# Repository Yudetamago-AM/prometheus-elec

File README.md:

# tanekonsat2022_runback

第19回（2023年度）種子島ロケットコンテストに出場予定の自動誘導ランバック機体の電装（回路・AW）ファイルを管理するレポジトリです。

構造のファイルは、<https://github.com/Yudetamago-AM/tanekonsat2022_runback>に、プログラムのファイルは色々のレポジトリに分散して管理してあります。

## KiCadで作業する時の注意

kicad2/lib/以下のtanekonsatというシンボルライブラリ・フットプリントライブラリを追加してあげる必要があります。

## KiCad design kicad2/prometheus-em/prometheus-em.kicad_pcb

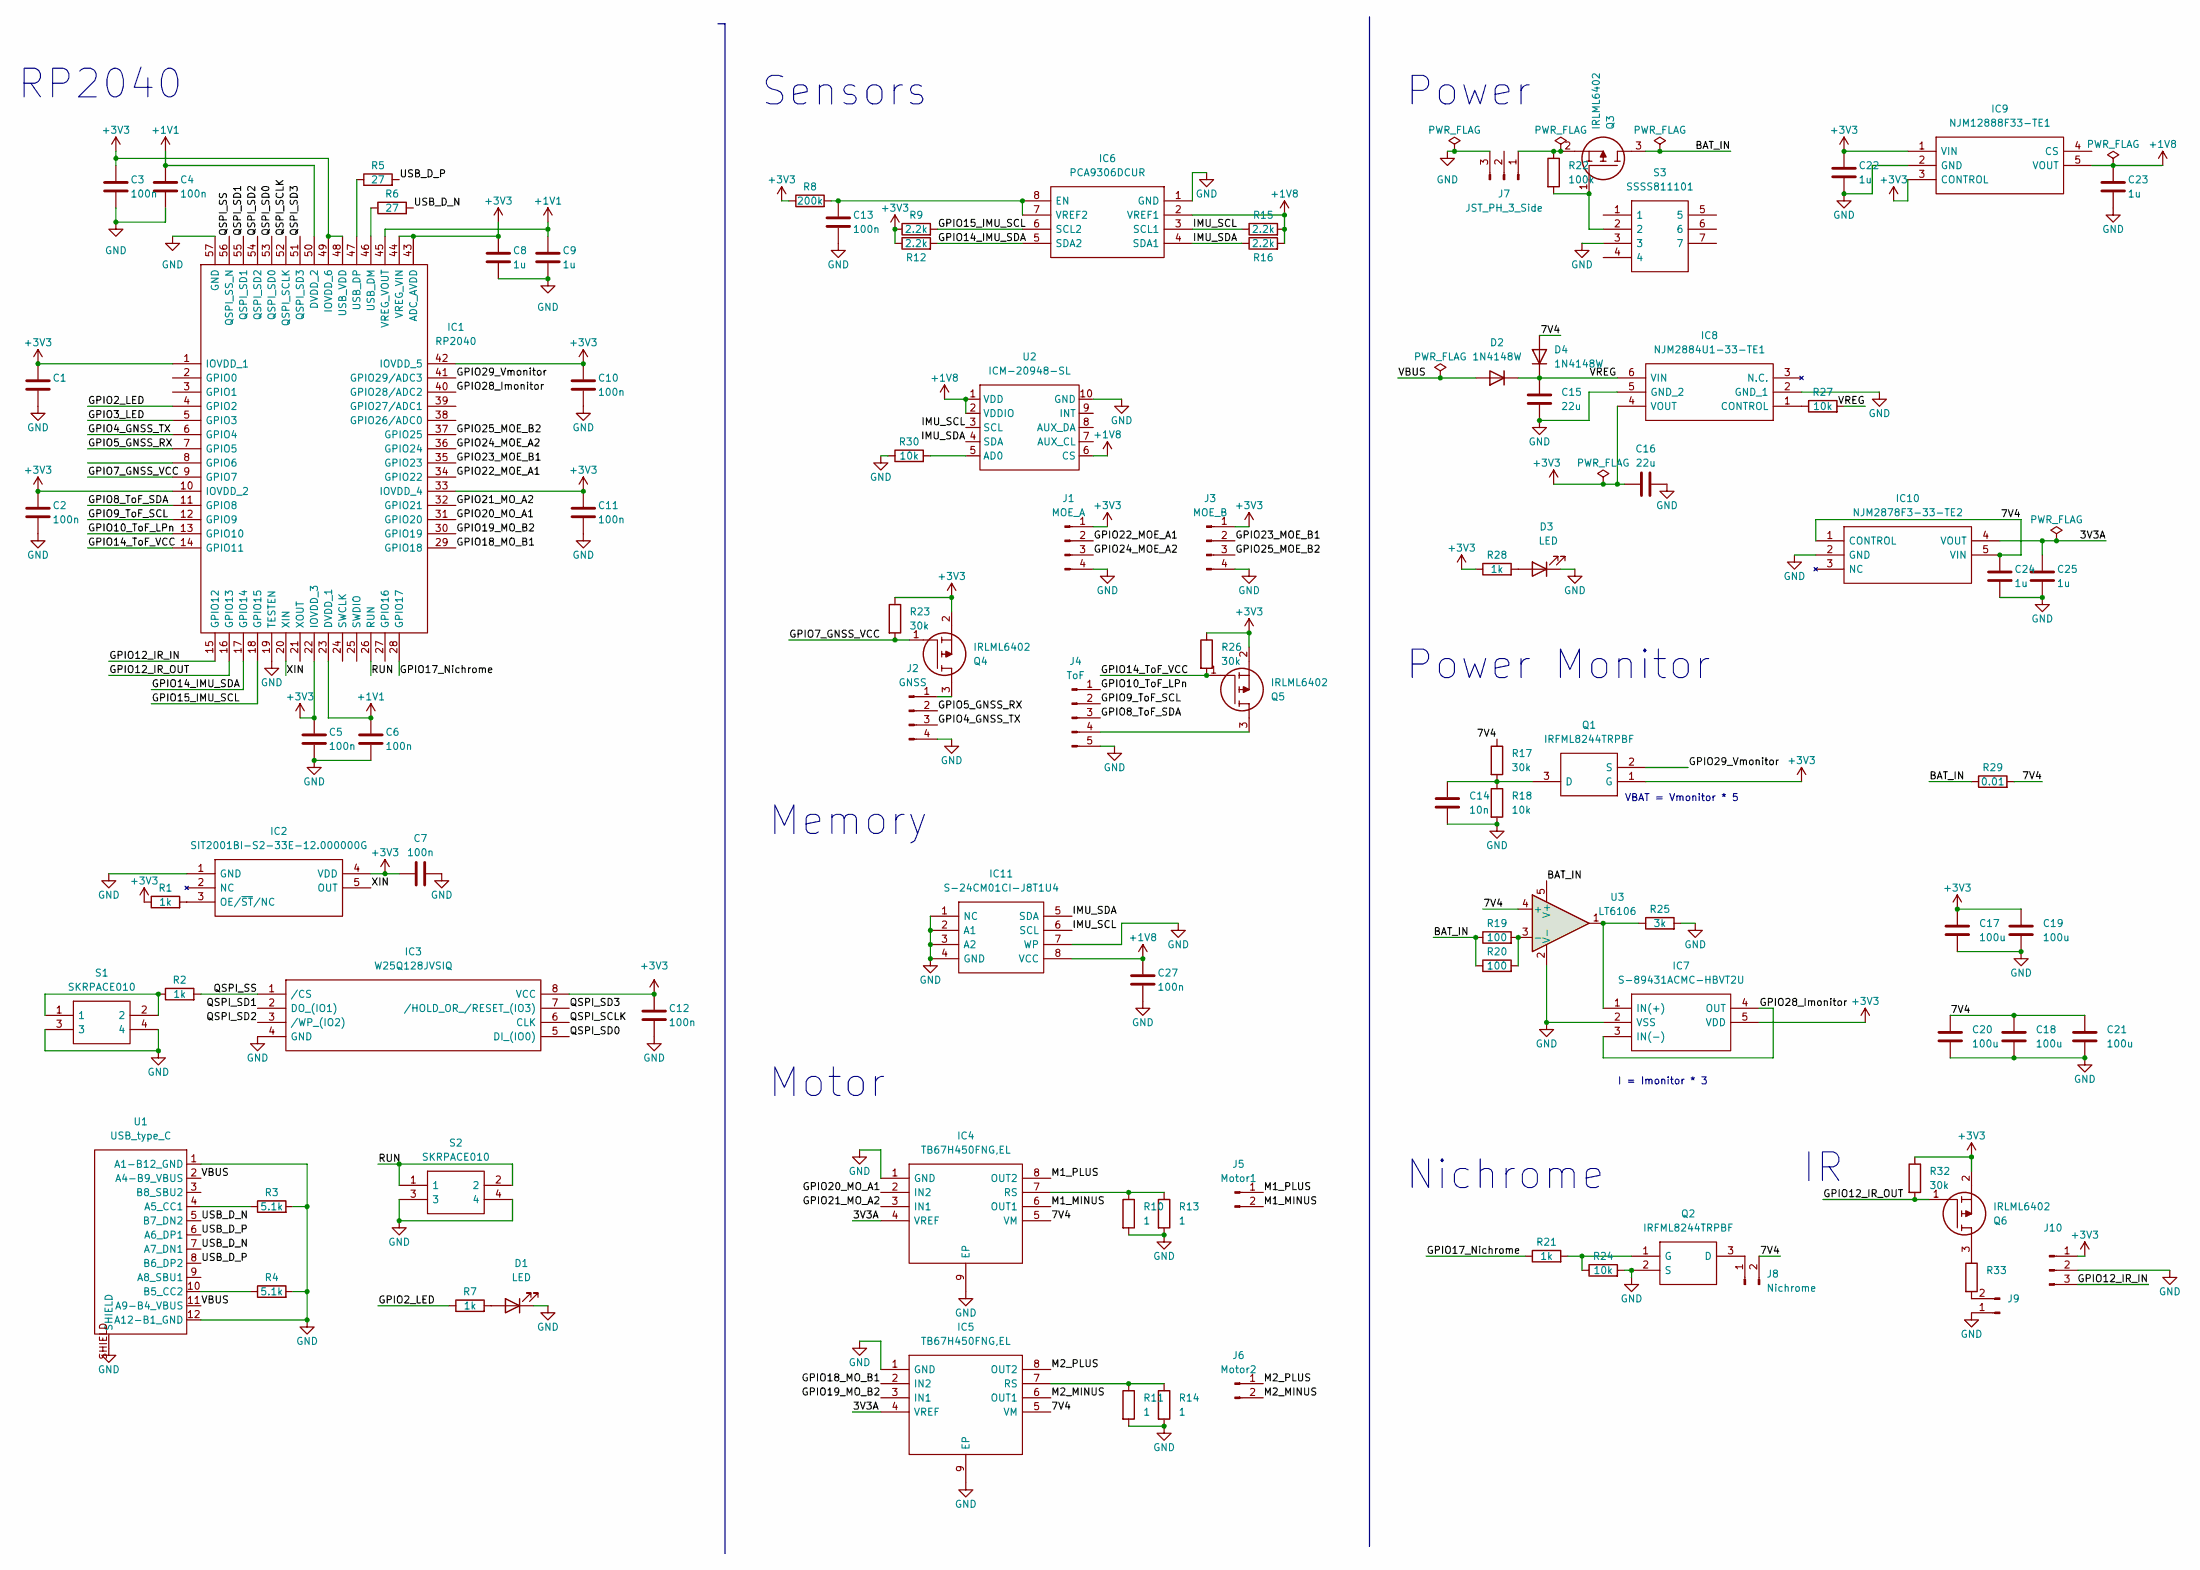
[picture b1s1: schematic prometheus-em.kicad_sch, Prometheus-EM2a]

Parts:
C1: LCSC C307331
C2, C3, C4, C7, C11, C12, C13: 100n; C_0402_1005Metric; LCSC C307331
C5, C6, C10, C27: 100n; C_0603_1608Metric
C8, C9, C22, C23, C24, C25: 1u; C_0402_1005Metric; LCSC C52923
C14: 10n; C_0402_1005Metric; LCSC C15195
C15, C16: 22u; C_0603_1608Metric; LCSC C59461
C17, C18, C19, C20, C21: 100u; C_1206_3216Metric
D1, D3: LED; LED_0603_1608Metric; LCSC C72041
D2, D4: 1N4148W; D_SOD-123
IC1: RP2040; QFN40P700X700X90-57N-D; Manufacturer_Part_Number RP2040; LCSC C2040
IC2: SIT2001BI-S2-33E-12.000000G; SOT95P280X130-5N; Manufacturer_Part_Number SIT2001BI-S2-33E-12.000000G; Mouser Part Number 788-2001BIS233E120G
IC3: W25Q128JVSIQ; SOIC127P790X216-8N; Manufacturer_Part_Number W25Q128JVSIQ; Mouser Part Number 454-W25Q128JVSIQ
IC4, IC5: TB67H450FNG,EL; SOIC127P600X175-9N; Manufacturer_Part_Number TB67H450FNG,EL
IC6: PCA9306DCUR; SOP50P310X90-8N; Manufacturer_Part_Number PCA9306DCUR; Mouser Part Number 595-PCA9306DCUR
IC7: S-89431ACMC-HBVT2U; SOT95P275X130-5N; Manufacturer_Part_Number S-89431ACMC-HBVT2U; Mouser Part Number 628-S89431ACMCHBVT2G
IC8: NJM2884U1-33-TE1; SOT-89-5-1; Manufacturer_Part_Number NJM2884U1-33-TE1; Mouser Part Number 513-NJM2884U1-33-TE1
IC9: NJM12888F33-TE1; SOT95P280X130-5N; Manufacturer_Part_Number NJM12888F33-TE1; Mouser Part Number 513-NJM12888F33-TE1
IC10: NJM2878F3-33-TE2; SOT65P210X100-5N; Manufacturer_Part_Number NJM2878F3-33-TE2; Mouser Part Number 513-NJM2878F3-33-TE2
IC11: S-24CM01CI-J8T1U4; SOT127P600X175-8N; Manufacturer_Part_Number S-24CM01CI-J8T1U4; Mouser Part Number 628-S-24CM01CIJ8T1U4
J1: MOE_A; PinHeader_1x04_P2.00mm_Vertical
J2: GNSS; JST_ZH_B4B-ZR_1x04_P1.50mm_Vertical
J3: MOE_B; PinHeader_1x04_P2.00mm_Vertical
J4: ToF; JST_ZH_B5B-ZR_1x05_P1.50mm_Vertical
J5: Motor1; PinHeader_1x02_P2.00mm_Vertical
J6: Motor2; PinHeader_1x02_P2.00mm_Vertical
J7: JST_PH_3_Side; JST_PH_S3B-PH-K_03x2.00mm_Angled
J8: Nichrome; PinHeader_1x02_P2.00mm_Vertical
J9, J10: (no value)
Q1, Q2: IRFML8244TRPBF; SOT95P237X112-3N; Manufacturer_Part_Number IRFML8244TRPBF; Mouser Part Number 942-IRFML8244TRPBF
Q3, Q4, Q5, Q6: IRLML6402; SOT95P237X112-3N; Manufacturer_Part_Number IRLML6402; Mouser Part Number N/A
R1, R2, R7, R21, R28: 1k; R_0402_1005Metric; LCSC C11702
R3, R4: 5.1k; R_0402_1005Metric; LCSC C25905
R5, R6: 27; R_0402_1005Metric; LCSC C174257
R8: 200k; R_0402_1005Metric; LCSC C25764
R9, R12, R15, R16: 2.2k; R_0402_1005Metric
R10, R11, R13, R14: 1; R_0603_1608Metric; LCSC C22936
R17, R23, R26, R32: 30k; R_0603_1608Metric; LCSC C22984
R18, R24, R27, R30: 10k; R_0402_1005Metric; LCSC C25744
R19, R20: 100; R_0402_1005Metric; LCSC C25076
R22: 100k; R_0402_1005Metric
R25: 3k; R_0603_1608Metric
R29: 0.01; R_1206_3216Metric
R33: (no value)
S1, S2: SKRPACE010; SMT_4.2X3.2_; Manufacturer_Part_Number SKRPACE010; Mouser Part Number 688-SKRPACE010
S3: SSSS811101; Manufacturer_Part_Number SSSS811101; Mouser Part Number 688-SSSS811101
U1: USB_type_C; USB_typeC_t
U2: ICM-20948-SL; ICM-20948_SL
U3: LT6106; SOT-23-5

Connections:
+1V1: C4.1, C6.1, C9.1, IC1.23 (DVDD_1), IC1.45 (VREG_VOUT), IC1.50 (DVDD_2)
+1V8: C23.1, C27.1, IC6.2 (VREF1), IC9.5 (VOUT), IC11.8 (VCC), R15.2, R16.2, U2.1 (VDD), U2.2 (VDDIO), U2.6 (CS)
+3V3: C1.1, C2.1, C3.1, C5.1, C7.1, C8.1, C10.1, C11.1, C12.1, C16.2, C17.1, C19.1, C22.1, IC1.1 (IOVDD_1), IC1.10 (IOVDD_2), IC1.22 (IOVDD_3), IC1.33 (IOVDD_4), IC1.42 (IOVDD_5), IC1.43 (ADC_AVDD), IC1.44 (VREG_VIN), IC1.48 (USB_VDD), IC1.49 (IOVDD_6), IC2.4 (VDD), IC3.8 (VCC), IC7.5 (VDD), IC8.4 (VOUT), IC9.1 (VIN), IC9.3 (CONTROL), J1.1, J3.1, J10.1, Q1.1 (G), Q4.2, Q5.2, Q6.2, R1.1, R8.1, R9.1, R12.1, R23.1, R26.1, R28.1, R32.1
/3V3A: C25.1, IC4.4 (VREF), IC5.4 (VREF), IC10.4 (VOUT)
/7V4: C18.1, C20.1, C21.1, C24.1, D4.2 (A), IC4.5 (VM), IC5.5 (VM), IC10.1 (CONTROL), IC10.5 (VIN), J8.2, R17.1, R29.2, U3.4 (+)
/BAT_IN: Q3.3, R19.1, R20.1, R29.1, U3.5 (V+)
/GPIO2_LED: IC1.4 (GPIO2), R7.1
/GPIO3_LED: IC1.5 (GPIO3)
/GPIO4_GNSS_TX: IC1.6 (GPIO4), J2.3
/GPIO5_GNSS_RX: IC1.7 (GPIO5), J2.2
/GPIO7_GNSS_VCC: IC1.9 (GPIO7), Q4.1, R23.2
/GPIO8_ToF_SDA: IC1.11 (GPIO8), J4.3
/GPIO9_ToF_SCL: IC1.12 (GPIO9), J4.2
/GPIO10_ToF_LPn: IC1.13 (GPIO10), J4.1
/GPIO12_IR_IN: IC1.15 (GPIO12), J10.3
/GPIO12_IR_OUT: IC1.16 (GPIO13), Q6.1, R32.2
/GPIO14_IMU_SDA: IC1.17 (GPIO14), IC6.5 (SDA2), R12.2
/GPIO14_ToF_VCC: IC1.14 (GPIO11), Q5.1, R26.2
/GPIO15_IMU_SCL: IC1.18 (GPIO15), IC6.6 (SCL2), R9.2
/GPIO17_Nichrome: IC1.28 (GPIO17), R21.1
/GPIO18_MO_B1: IC1.29 (GPIO18), IC5.2 (IN2)
/GPIO19_MO_B2: IC1.30 (GPIO19), IC5.3 (IN1)
/GPIO20_MO_A1: IC1.31 (GPIO20), IC4.2 (IN2)
/GPIO21_MO_A2: IC1.32 (GPIO21), IC4.3 (IN1)
/GPIO22_MOE_A1: IC1.34 (GPIO22), J1.2
/GPIO23_MOE_B1: IC1.35 (GPIO23), J3.2
/GPIO24_MOE_A2: IC1.36 (GPIO24), J1.3
/GPIO25_MOE_B2: IC1.37 (GPIO25), J3.3
/GPIO28_Imonitor: IC1.40 (GPIO28/ADC2), IC7.3 (IN(-)), IC7.4 (OUT)
/GPIO29_Vmonitor: IC1.41 (GPIO29/ADC3), Q1.2 (S)
/IMU_SCL: IC6.3 (SCL1), IC11.6 (SCL), R15.1, U2.3 (SCL)
/IMU_SDA: IC6.4 (SDA1), IC11.5 (SDA), R16.1, U2.4 (SDA)
/M1_MINUS: IC4.6 (OUT1), J5.2
/M1_PLUS: IC4.8 (OUT2), J5.1
/M2_MINUS: IC5.6 (OUT1), J6.2
/M2_PLUS: IC5.8 (OUT2), J6.1
/QSPI_SCLK: IC1.52 (QSPI_SCLK), IC3.6 (CLK)
/QSPI_SD0: IC1.53 (QSPI_SD0), IC3.5 (DI_(IO0))
/QSPI_SD1: IC1.55 (QSPI_SD1), IC3.2 (DO_(IO1))
/QSPI_SD2: IC1.54 (QSPI_SD2), IC3.3 (/WP_(IO2))
/QSPI_SD3: IC1.51 (QSPI_SD3), IC3.7 (/HOLD_OR_/RESET_(IO3))
/QSPI_SS: IC1.56 (QSPI_SS_N), IC3.1 (/CS), R2.2
/RUN: IC1.26 (RUN), S2.1, S2.2
/USB_D_N: R6.2, U1.5 (B7_DN2), U1.7 (A7_DN1)
/USB_D_P: R5.2, U1.6 (A6_DP1), U1.8 (B6_DP2)
/VBUS: D2.2 (A), U1.2 (A4-B9_VBUS), U1.11 (A9-B4_VBUS)
/VREG: C15.1, D2.1 (K), D4.1 (K), IC8.6 (VIN), R27.2
/XIN: IC1.20 (XIN), IC2.5 (OUT)
GND: C1.2, C2.2, C3.2, C4.2, C5.2, C6.2, C7.2, C8.2, C9.2, C10.2, C11.2, C12.2, C13.2, C14.2, C15.2, C16.1, C17.2, C18.2, C19.2, C20.2, C21.2, C22.2, C23.2, C24.2, C25.2, C27.2, D1.1 (K), D3.1 (K), IC1.19 (TESTEN), IC1.57 (GND), IC2.1 (GND), IC3.4 (GND), IC4.1 (GND), IC4.9 (EP), IC5.1 (GND), IC5.9 (EP), IC6.1 (GND), IC7.2 (VSS), IC8.2 (GND_1), IC8.5 (GND_2), IC9.2 (GND), IC10.2 (GND), IC11.1 (NC), IC11.2 (A1), IC11.3 (A2), IC11.4 (GND), IC11.7 (WP), J1.4, J2.4, J3.4, J4.5, J7.3, J9.1, J10.2, Q2.2 (S), R3.2, R4.2, R10.2, R11.2, R13.2, R14.2, R18.2, R24.2, R25.2, R30.1, S1.3, S1.4, S2.3, S2.4, S3.3, U1.1 (A1-B12_GND), U1.12 (A12-B1_GND), U1.SHIELD, U2.10 (GND), U3.2 (V-)
unnamed: C13.1, IC6.7 (VREF2), IC6.8 (EN), R8.2
unnamed: C14.1, Q1.3 (D), R17.2, R18.1
unnamed: D1.2 (A), R7.2
unnamed: D3.2 (A), R28.2
unnamed: IC1.46 (USB_DM), R6.1
unnamed: IC1.47 (USB_DP), R5.1
unnamed: IC2.3 (OE/~ST/NC), R1.2
unnamed: IC4.7 (RS), R10.1, R13.1
unnamed: IC5.7 (RS), R11.1, R14.1
unnamed: IC7.1 (IN(+)), R25.1, U3.1
unnamed: IC8.1 (CONTROL), R27.1
unnamed: J2.1, Q4.3
unnamed: J4.4, Q5.3
unnamed: J7.1, Q3.2, R22.1
unnamed: J8.1, Q2.3 (D)
unnamed: J9.2, R33.2
unnamed: Q2.1 (G), R21.2, R24.1
unnamed: Q3.1, R22.2, S3.2
unnamed: Q6.3, R33.1
unnamed: R2.1, S1.1, S1.2
unnamed: R3.1, U1.4 (A5_CC1)
unnamed: R4.1, U1.10 (B5_CC2)
unnamed: R19.2, R20.2, U3.3 (-)
unnamed: R30.2, U2.5 (AD0)

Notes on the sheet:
Power
RP2040
Nichrome
VBAT = Vmonitor * 5
Sensors
Motor
Memory
I = Imonitor * 3
Power Monitor

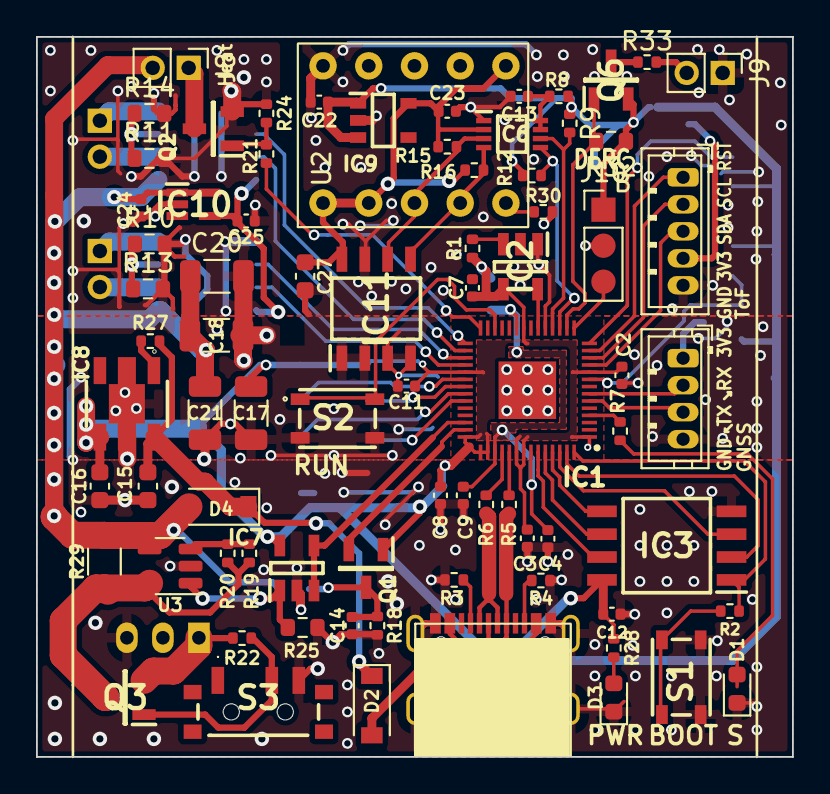
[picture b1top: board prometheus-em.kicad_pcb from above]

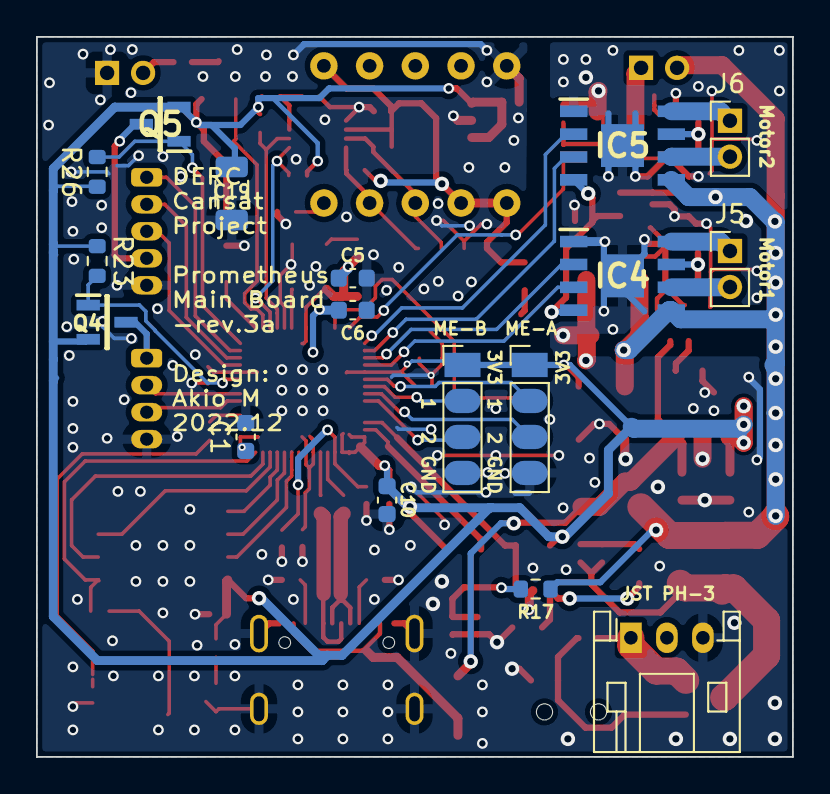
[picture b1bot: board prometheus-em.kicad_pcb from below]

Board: 2 copper layers, 42.0 x 40.0 mm, 95 parts (17 on the bottom side), 72 nets.

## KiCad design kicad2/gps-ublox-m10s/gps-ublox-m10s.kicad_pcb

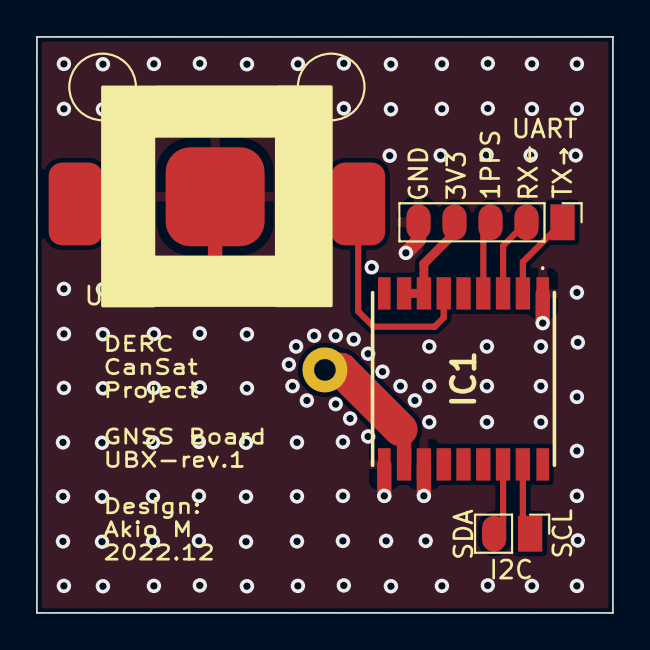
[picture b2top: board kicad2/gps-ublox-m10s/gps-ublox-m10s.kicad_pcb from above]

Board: 2 copper layers, 32.0 x 32.0 mm, 5 parts (1 on the bottom side), 9 nets.

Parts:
ANT1: CGGBP.25.4.A.02; CGGBP254A02
IC1: MAX-M10S-00B; MAXM10S00B
J1: Conn_01x05_Male; PinHeader_1x05_P2.00mm_Vertical
J2: I2C; PinHeader_1x02_P2.00mm_Vertical
U1: CR1025; CR1025_Holder

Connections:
+3V0: IC1.6 (V_BCKP), U1.2 (plus)
+3V3: IC1.7 (V_IO), IC1.8 (VCC), J1.4
/GNSS_1PPS: IC1.4 (TIMEPULSE), J1.3
/GNSS_RX: IC1.3 (RXD), J1.2
/GNSS_TX: IC1.2 (TXD), J1.1
/SCL: IC1.17 (SCL), J2.1
/SDA: IC1.16 (SDA), J2.2
GND: IC1.1 (GND_1), IC1.10 (GND_2), IC1.12 (GND_3), J1.5, U1.1 (minus)
unnamed: ANT1.1, IC1.11 (RF_IN)

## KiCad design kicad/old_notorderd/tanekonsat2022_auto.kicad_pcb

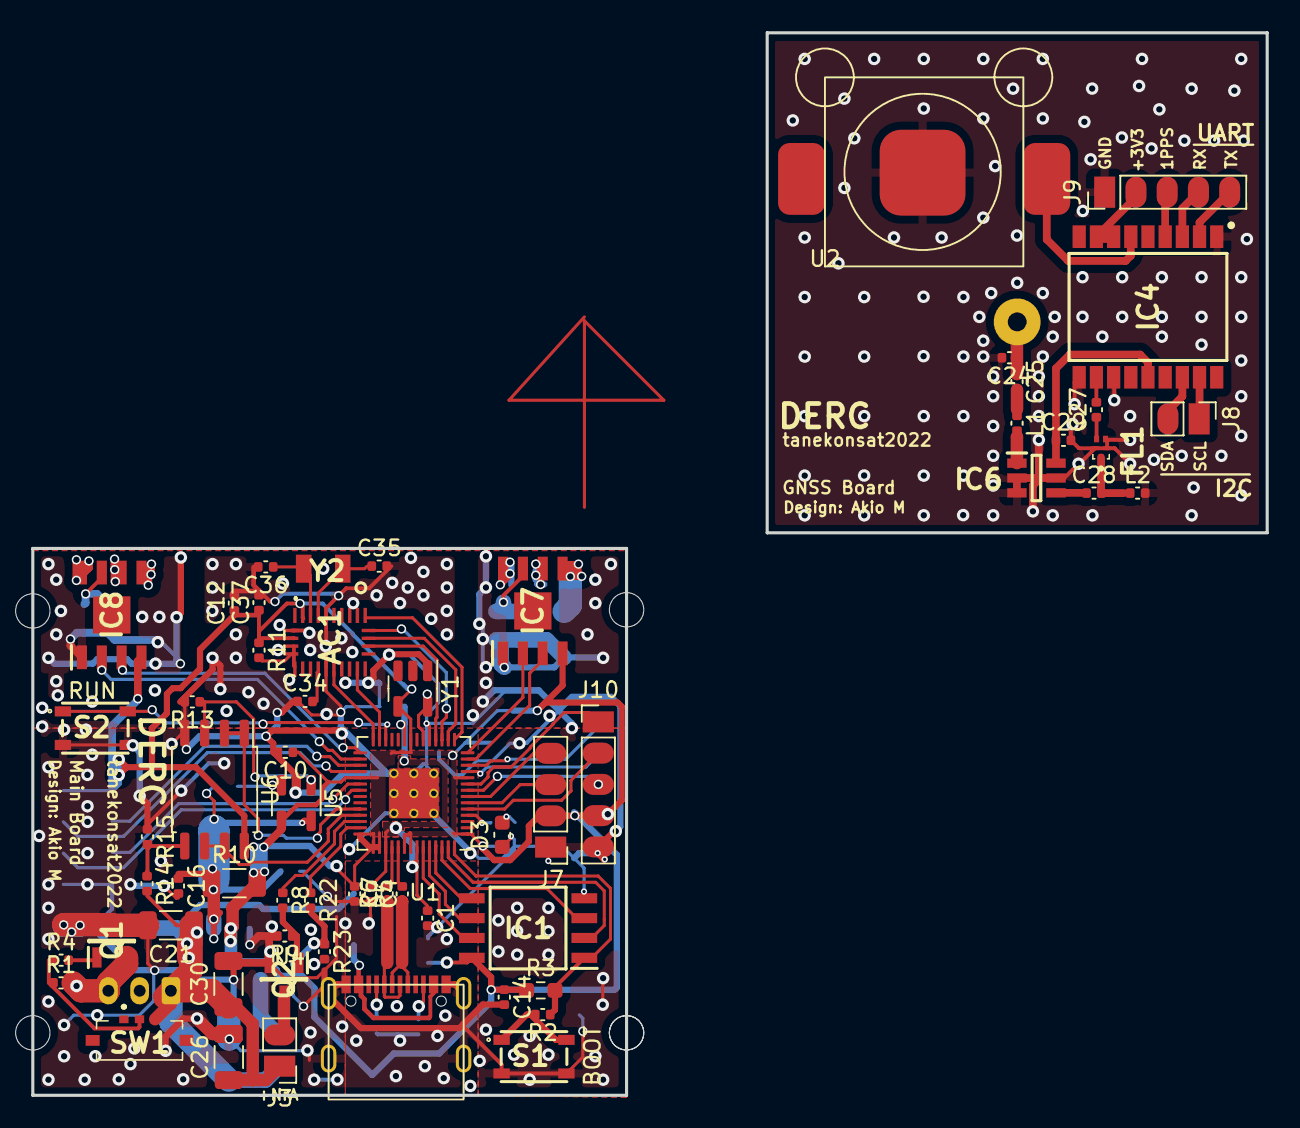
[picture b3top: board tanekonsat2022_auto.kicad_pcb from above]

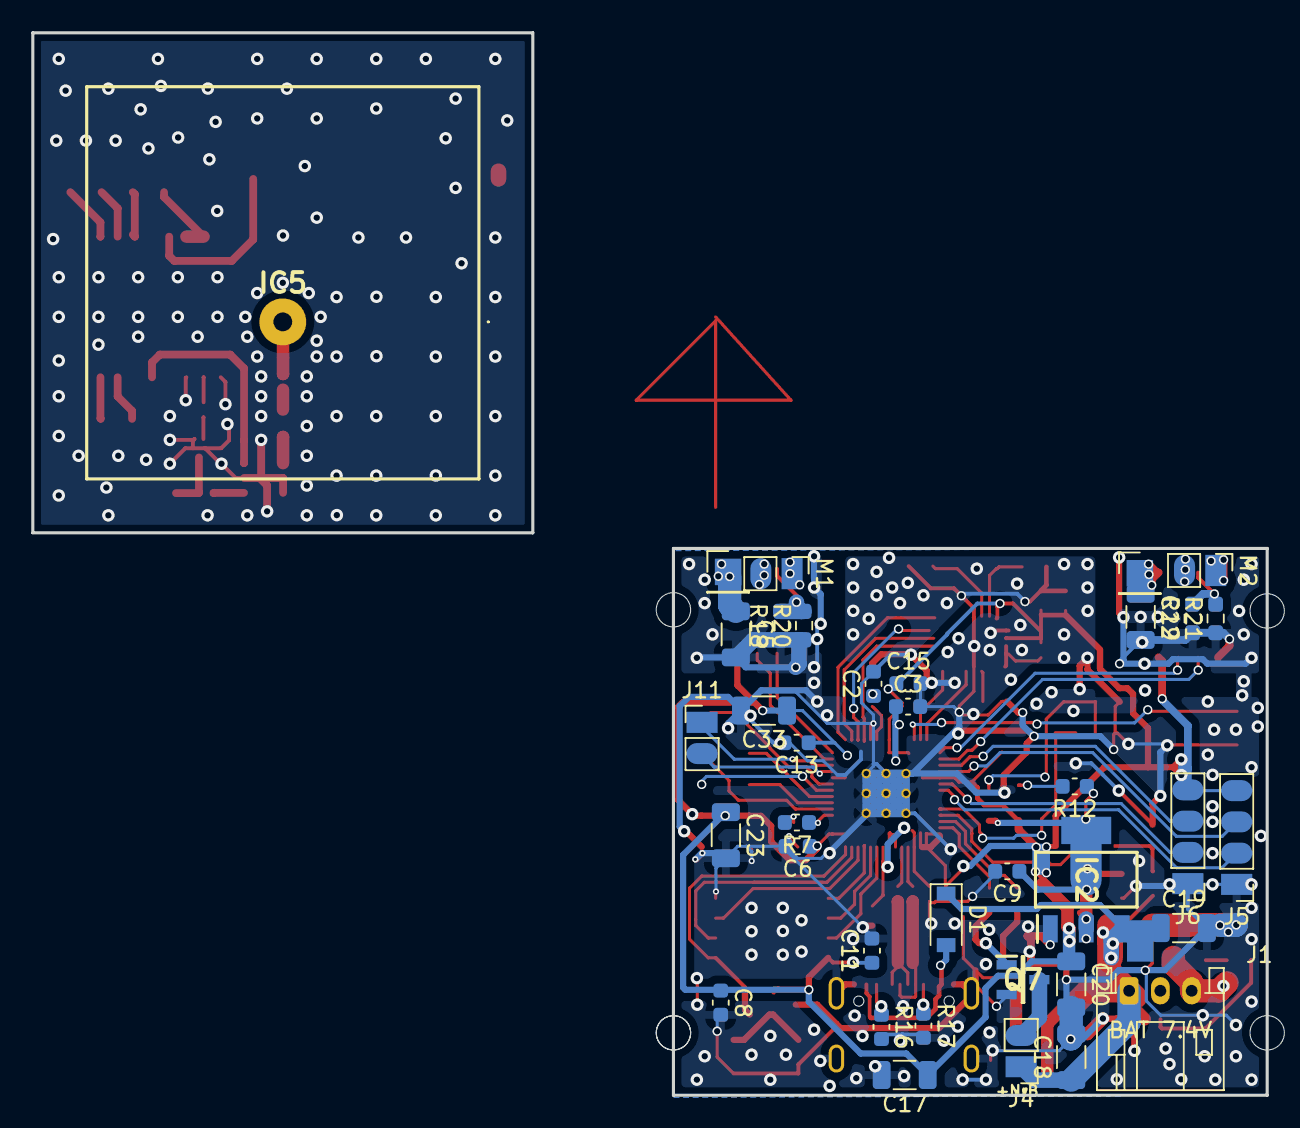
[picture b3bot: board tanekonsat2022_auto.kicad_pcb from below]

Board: 2 copper layers, 38.0 x 35.0 mm, 96 parts (35 on the bottom side), 80 nets.

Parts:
AC1: BNO085
C1, C10, C12, C14, C34, C37: 100n; C_0402_1005Metric
C2: 10p; C_0603_1608Metric
C3, C6, C8, C11, C13, C15: 100n; C_0603_1608Metric
C4, C7, C16: 1u; C_0402_1005Metric
C5, C17, C18, C19, C20, C21, C22, C23, C26, C30, C33: 100u; C_1206_3216Metric
C9: 1u; C_0603_1608Metric
C24: 1p; C_0402_1005Metric
C25, C28: 100p; C_0402_1005Metric
C27: 120p; C_0402_1005Metric
C29: 470p; C_0402_1005Metric
C35, C36: 22p; C_0402_1005Metric
D1: 1N4148W; D_SOD-123
D3: LED; C_0603_1608Metric
FL1: SAFEA1G58KA0F00R15
IC1: W25Q128JVSIQ; SOIC127P790X216-8N
IC2: ADP3338AKCZ-3.3-RL; SOT230P700X180-4N
IC4: TESEO-LIV3F; SON110P970X1010X230-18N
IC5: CGGBPD.25.A; CGGBPD25A
IC6: MAX2641EUT+T; SOT95P280X145-6N
IC7, IC8: TB67H450FNG,EL; SOIC127P600X175-9N
J1: Conn_01x02_Male; JST_PH_S3B-PH-K_1x03_P2.00mm_Horizontal
J3, J4: Conn_01x02_Male; PinHeader_1x02_P2.00mm_Vertical
J5, J6: Conn_01x04_Male; PinHeader_1x04_P2.00mm_Vertical
J7: Conn_01x04_Female; PinHeader_1x04_P2.00mm_Vertical
J8, J11: Conn_01x02_Female; PinHeader_1x02_P2.00mm_Vertical
J9, J10: Conn_01x05_Female; PinHeader_1x05_P2.00mm_Vertical
L1: 5.6n; C_0402_1005Metric
L2: 6.8n; C_0402_1005Metric
M1, M2: Motor_DC; PinHeader_1x02_P2.00mm_Vertical
Q1, Q2, Q7: Q_NMOS_DGS; SOT95P237X112-3N
R1, R4, R9, R11, R23: 10k; C_0402_1005Metric
R2, R8, R13, R15, R22: 1k; C_0402_1005Metric
R3: DNF; R_0603_1608Metric_Pad0.98x0.95mm_HandSolder
R5, R6: 27; C_0402_1005Metric
R7: 1k; C_0603_1608Metric
R10: 0.01; R_1206_3216Metric
R12: 100; C_0603_1608Metric
R14: 3k; C_0402_1005Metric
R16, R17: 5.1k; C_0603_1608Metric
R18, R19, R20, R21: R; R_0603_1608Metric_Pad0.98x0.95mm_HandSolder
S1, S2: SKRPACE010; SMT_4.2X3.2_
SW1: SW_DIP_x01; SSAJ120100
U1: RP2040; RP2040-QFN-56
U2: CR1025; CR1025_Holder
U4: USB_type_C; USB_typeC_t
U5: LT6106; SOT-23-5
U6: Opamp_Dual; SSOP-8_5.25x5.24mm_P1.27mm
Y1: SIT2001BI-S2-33E-12.000000D; SOT-23-5
Y2: FC-135_32.768KHz_7pF_+_-20ppm; FC-135

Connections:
+1V1: C1.1, C3.1, C4.1, U1.23 (DVDD), U1.45 (VREG_VOUT), U1.50 (DVDD)
+3V0: IC4.6 (VBATT), U2.2 (plus)
+3V3: AC1.3 (VDD), AC1.28 (VDDIO), C6.1, C7.1, C8.1, C10.1, C11.1, C12.1, C13.1, C14.1, C15.1, C17.1, C20.1, C23.1, C33.1, C37.1, IC1.8 (VCC), IC4.7 (VCC_IO), IC4.8 (VCC), IC7.4 (VREF), IC8.4 (VREF), J5.4, J6.4, J7.2, J9.2, J10.4, R3.1, R10.2, R11.1, U1.1 (IOVDD), U1.10 (IOVDD), U1.22 (IOVDD), U1.33 (IOVDD), U1.42 (IOVDD), U1.43 (ADC_AVDD), U1.44 (VREG_IN), U1.48 (USB_VDD), U1.49 (IOVDD), U5.4 (+), U6.8 (V+), Y1.4 (VDD)
/3V3_REG_OUT: C9.1, C16.1, IC2.2 (OUT_1), IC2.4 (OUT_2), R10.1, R12.1, U5.5 (V+)
/+7V4: C5.1, C18.1, C19.1, C21.1, C22.1, C26.1, C30.1, D1.1 (K), IC2.3 (IN), IC7.5 (VM), IC8.5 (VM), J1.1, J3.1, J4.1, R14.2, SW1.2
/GNSS_1PPS: IC4.4 (1PPS), J9.3
/GPIO2_LED: R7.1, U1.4 (GPIO2)
/GPIO3_ToF_RST: J10.2, U1.5 (GPIO3)
/GPIO4_GNSS_RX: IC4.3 (RX), J7.3, J9.4, U1.6 (GPIO4)
/GPIO5_GNSS_TX: IC4.2 (TX), J7.4, J9.5, U1.7 (GPIO5)
/GPIO6_ToF_SDA: J10.3, U1.8 (GPIO6)
/GPIO7_ToF_SCL: J10.1, U1.9 (GPIO7)
/GPIO8_I2C_EXT_SDA: J11.2, U1.11 (GPIO8)
/GPIO9_I2C_EXT_SCL: J11.1, U1.12 (GPIO9)
/GPIO10_MO_A_1: IC7.3 (IN1), U1.13 (GPIO10)
/GPIO11_MO_A_2: IC7.2 (IN2), U1.14 (GPIO11)
/GPIO12_IMU_MISO: AC1.20 (H_SDA/H_MISO/TX), U1.15 (GPIO12)
/GPIO13_IMU_CS: AC1.18 (H_CSN), U1.16 (GPIO13)
/GPIO14_IMU_SCK: AC1.19 (H_SCL/SCK/RX), U1.17 (GPIO14)
/GPIO15_IMU_MOSI: AC1.17 (SA0/H_MOSI), U1.18 (GPIO15)
/GPIO16_IMU_INT: AC1.14 (H_INTN), U1.27 (GPIO16)
/GPIO17_IMU_RST: AC1.11 (NRST), U1.28 (GPIO17)
/GPIO18_MO_B_1: IC8.3 (IN1), U1.29 (GPIO18)
/GPIO19_MO_B_2: IC8.2 (IN2), U1.30 (GPIO19)
/GPIO20_MOE_A_1: J6.3, U1.31 (GPIO20)
/GPIO21_MOE_B_1: J5.3, U1.32 (GPIO21)
/GPIO22_MOE_A_2: J6.2, U1.34 (GPIO22)
/GPIO23_MOE_B_2: J5.2, U1.35 (GPIO23)
/GPIO26_ADC_I_monitor: U1.38 (GPIO26_ADC0), U6.1, U6.2 (-)
/GPIO27_ADC_V_monitor: U1.39 (GPIO27_ADC1), U6.6 (-), U6.7
/GPIO28_NichromeA: R8.1, U1.40 (GPIO28_ADC2)
/GPIO29_NichromeB: R22.1, U1.41 (GPIO29_ADC3)
/M1_MINUS: IC7.6 (OUT1), M1.2 (-)
/M1_PLUS: IC7.8 (OUT2), M1.1 (+)
/M2_MINUS: IC8.6 (OUT1), M2.2 (-)
/M2_PLUS: IC8.8 (OUT2), M2.1 (+)
/QSPI_SCLK: IC1.6 (CLK), U1.52 (QSPI_SCLK)
/QSPI_SD0: IC1.5 (DI_(IO0)), U1.53 (QSPI_SD0)
/QSPI_SD1: IC1.2 (DO_(IO1)), U1.55 (QSPI_SD1)
/QSPI_SD2: IC1.3 (/WP_(IO2)), U1.54 (QSPI_SD2)
/QSPI_SD3: IC1.7 (/HOLD_OR_/RESET_(IO3)), U1.51 (QSPI_SD3)
/QSPI_SS: IC1.1 (/CS), R2.1, R3.2, U1.56 (QSPI_SS)
/RUN: S2.1, S2.2, U1.26 (RUN)
/USB_D+: R5.1, U4.6 (A6_DP1), U4.8 (B6_DP2)
/USB_D-: R6.1, U4.5 (B7_DN2), U4.7 (A7_DN1)
/VBUS: D1.2 (A), U4.2 (A4-B9_VBUS), U4.11 (A9-B4_VBUS)
/VCC_RF: C29.1, IC4.14 (VCC_RF), IC6.6 (VCC)
/XIN: C2.1, U1.20 (XIN), Y1.5 (OUT)
/~USB_BOOT: R2.2, S1.1, S1.2
GND: AC1.2 (GND_1), AC1.10 (CLKSEL0), AC1.25 (GND_2), C1.2, C2.2, C3.2, C4.2, C5.2, C6.2, C7.2, C8.2, C9.2, C10.2, C11.2, C12.2, C13.2, C14.2, C15.2, C16.2, C17.2, C18.2, C19.2, C20.2, C21.2, C22.2, C23.2, C24.2, C26.2, C29.2, C30.2, C33.2, C34.1, C35.2, C36.2, C37.2, D3.1 (K), FL1.2 (GND_1), FL1.3 (GND_2), FL1.5 (GND_3), IC1.4 (GND), IC2.1 (GND), IC4.1 (GND), IC4.10 (GND_RF_1), IC4.12 (GND_RF_2), IC6.2 (GND_1), IC6.3 (GND_2), IC6.5 (GND_3), IC7.1 (GND), IC8.1 (GND), J5.1, J6.1, J7.1, J9.1, J10.5, L2.2, Q1.3 (D), Q2.2 (S), Q7.2 (S), R9.2, R13.2, R15.1, R16.2, R17.2, R18.1, R19.1, R20.1, R21.1, R23.2, S1.3, S1.4, S2.3, S2.4, U1.19 (TESTEN), U1.57 (GND), U2.1 (minus), U4.1 (A1-B12_GND), U4.12 (A12-B1_GND), U4.SHIELD, U5.2 (V-), U6.4 (V-), Y1.1 (GND)
GND1: J1.3 (Pin_2), Q1.2 (S), R1.2
unnamed: AC1.4 (BOOTN), AC1.5 (PS1), AC1.6 (PS0/WAKE), R11.2
unnamed: AC1.9 (CAP), C34.2
unnamed: AC1.26 (XOUT32/CLKSEL1), C35.1, Y2.1
unnamed: AC1.27 (XIN32), C36.1, Y2.2
unnamed: C24.1, C25.1, IC5.1
unnamed: C25.2, L1.1
unnamed: C27.1, FL1.4 (OUT)
unnamed: C27.2, IC4.11 (RF_IN)
unnamed: C28.1, IC6.4 (RFOUT)
unnamed: C28.2, FL1.1 (IN), L2.1
unnamed: D3.2 (A), R7.2
unnamed: IC4.16 (SDA), J8.2
unnamed: IC4.17 (SCL), J8.1
unnamed: IC6.1 (RFIN), L1.2
unnamed: IC7.7 (RS), R18.2, R20.2
unnamed: IC8.7 (RS), R19.2, R21.2
unnamed: J3.2, Q2.3 (D)
unnamed: J4.2, Q7.3 (D)
unnamed: Q1.1 (G), R4.2
unnamed: Q2.1 (G), R8.2, R9.1
unnamed: Q7.1 (G), R22.2, R23.1
unnamed: R1.1, R4.1, SW1.C1
unnamed: R5.2, U1.47 (USB_DP)
unnamed: R6.2, U1.46 (USB_DM)
unnamed: R12.2, U5.3 (-)
unnamed: R13.1, U5.1, U6.3 (+)
unnamed: R14.1, R15.2, U6.5 (+)
unnamed: R16.1, U4.10 (B5_CC2)
unnamed: R17.1, U4.4 (A5_CC1)

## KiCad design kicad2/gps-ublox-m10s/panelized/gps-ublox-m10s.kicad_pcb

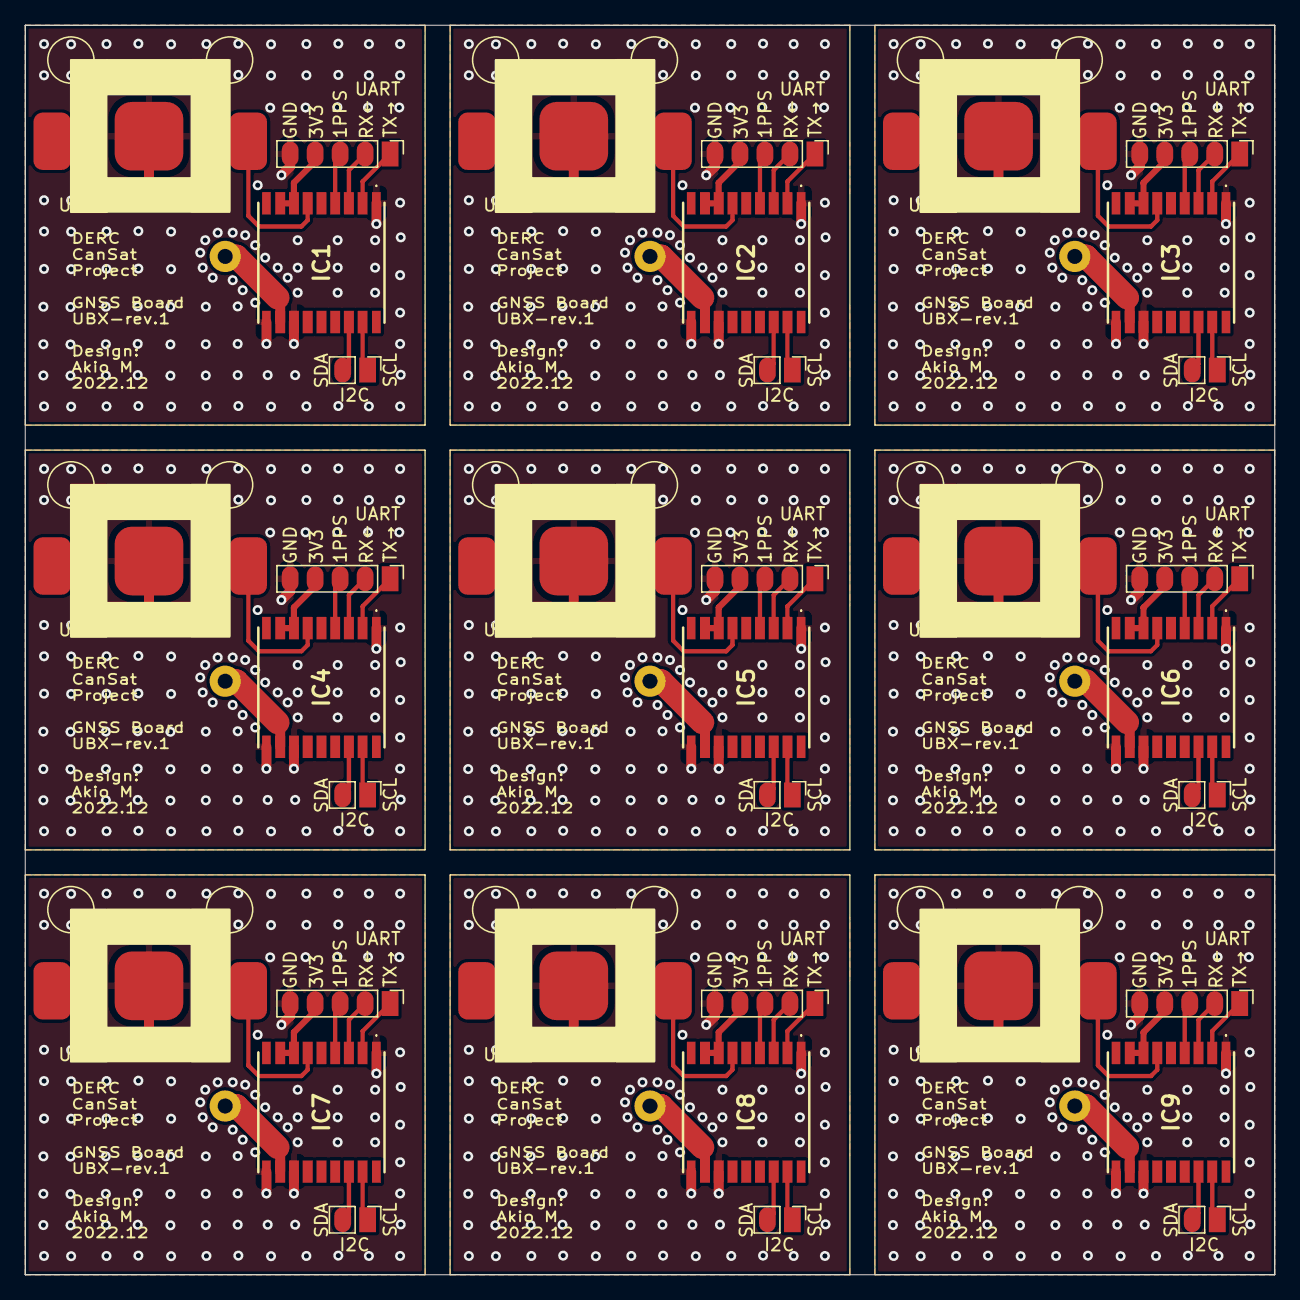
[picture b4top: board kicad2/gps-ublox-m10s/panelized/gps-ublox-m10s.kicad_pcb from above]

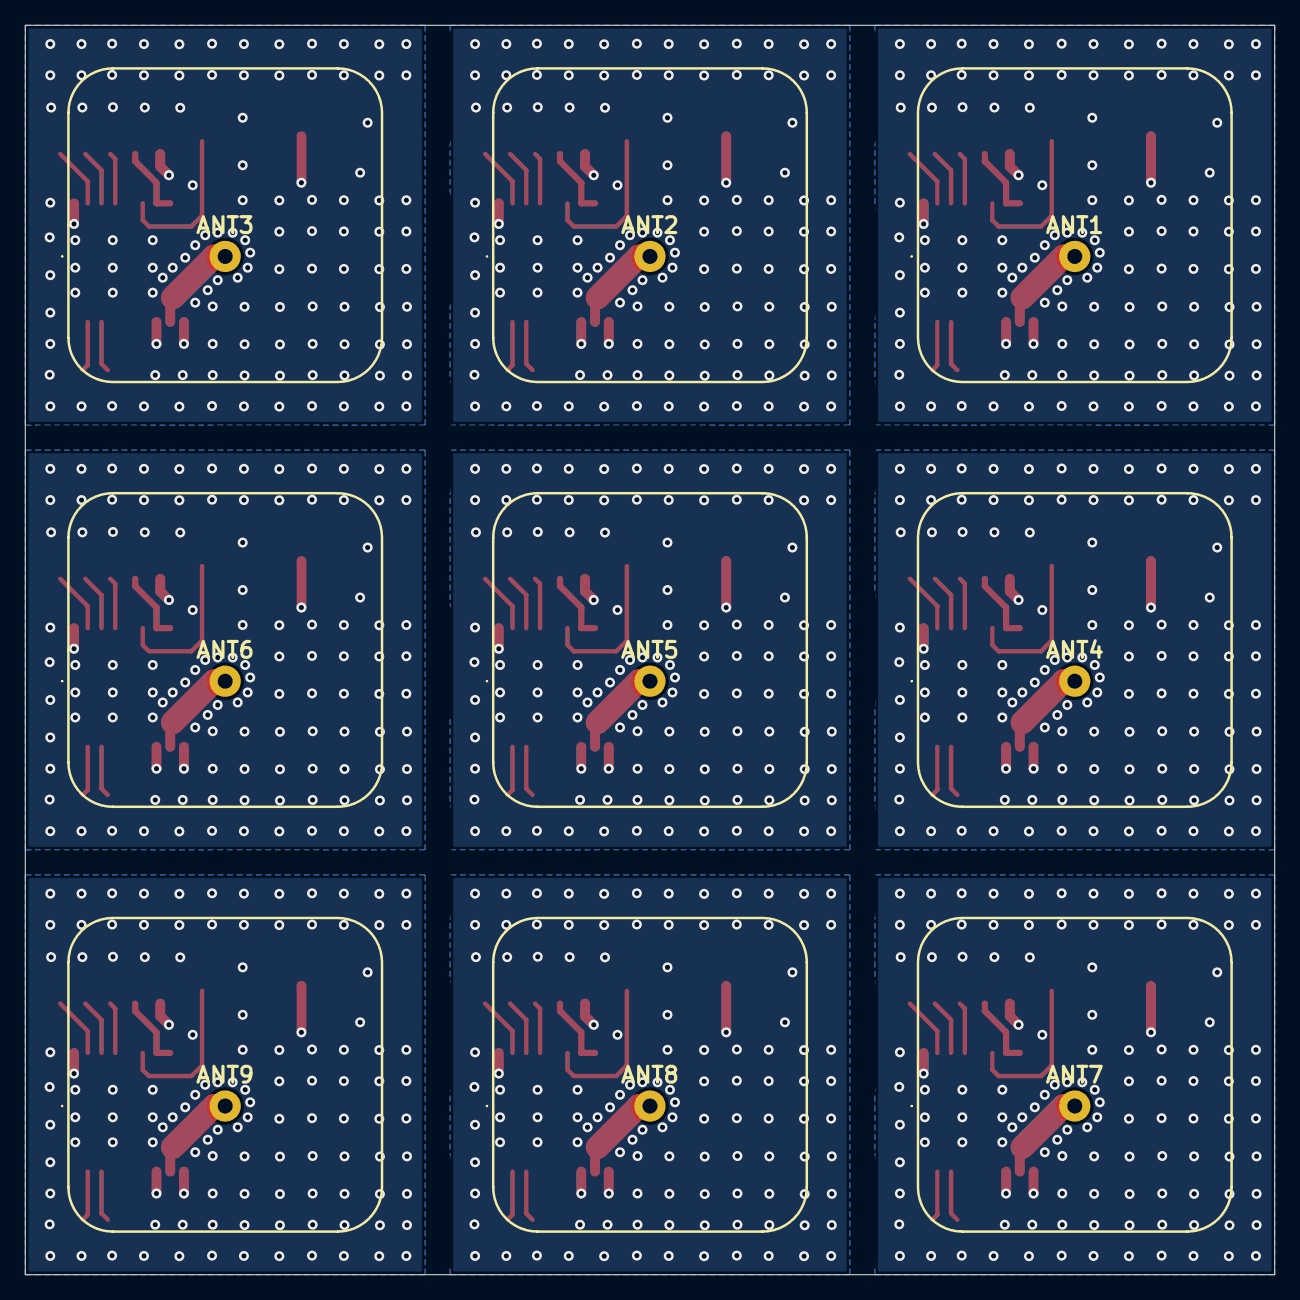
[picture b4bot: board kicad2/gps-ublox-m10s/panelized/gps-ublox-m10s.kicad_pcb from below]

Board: 2 copper layers, 100.0 x 100.0 mm, 45 parts (9 on the bottom side), 9 nets.

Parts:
ANT1, ANT2, ANT3, ANT4, ANT5, ANT6, ANT7, ANT8, ANT9: CGGBP.25.4.A.02; CGGBP254A02
IC1, IC2, IC3, IC4, IC5, IC6, IC7, IC8, IC9: MAX-M10S-00B; MAXM10S00B
J1, J3, J5, J7, J9, J11, J13, J15, J17: Conn_01x05_Male; PinHeader_1x05_P2.00mm_Vertical
J2, J4, J6, J8, J10, J12, J14, J16, J18: I2C; PinHeader_1x02_P2.00mm_Vertical
U1, U2, U3, U4, U5, U6, U7, U8, U9: CR1025; CR1025_Holder

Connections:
+3V0: IC1.6 (V_BCKP), IC2.6 (V_BCKP), IC3.6 (V_BCKP), IC4.6 (V_BCKP), IC5.6 (V_BCKP), IC6.6 (V_BCKP), IC7.6 (V_BCKP), IC8.6 (V_BCKP), IC9.6 (V_BCKP), U1.2 (plus), U2.2 (plus), U3.2 (plus), U4.2 (plus), U5.2 (plus), U6.2 (plus), U7.2 (plus), U8.2 (plus), U9.2 (plus)
+3V3: IC1.7 (V_IO), IC1.8 (VCC), IC2.7 (V_IO), IC2.8 (VCC), IC3.7 (V_IO), IC3.8 (VCC), IC4.7 (V_IO), IC4.8 (VCC), IC5.7 (V_IO), IC5.8 (VCC), IC6.7 (V_IO), IC6.8 (VCC), IC7.7 (V_IO), IC7.8 (VCC), IC8.7 (V_IO), IC8.8 (VCC), IC9.7 (V_IO), IC9.8 (VCC), J1.4, J3.4, J5.4, J7.4, J9.4, J11.4, J13.4, J15.4, J17.4
/GNSS_1PPS: IC1.4 (TIMEPULSE), IC2.4 (TIMEPULSE), IC3.4 (TIMEPULSE), IC4.4 (TIMEPULSE), IC5.4 (TIMEPULSE), IC6.4 (TIMEPULSE), IC7.4 (TIMEPULSE), IC8.4 (TIMEPULSE), IC9.4 (TIMEPULSE), J1.3, J3.3, J5.3, J7.3, J9.3, J11.3, J13.3, J15.3, J17.3
/GNSS_RX: IC1.3 (RXD), IC2.3 (RXD), IC3.3 (RXD), IC4.3 (RXD), IC5.3 (RXD), IC6.3 (RXD), IC7.3 (RXD), IC8.3 (RXD), IC9.3 (RXD), J1.2, J3.2, J5.2, J7.2, J9.2, J11.2, J13.2, J15.2, J17.2
/GNSS_TX: IC1.2 (TXD), IC2.2 (TXD), IC3.2 (TXD), IC4.2 (TXD), IC5.2 (TXD), IC6.2 (TXD), IC7.2 (TXD), IC8.2 (TXD), IC9.2 (TXD), J1.1, J3.1, J5.1, J7.1, J9.1, J11.1, J13.1, J15.1, J17.1
/SCL: IC1.17 (SCL), IC2.17 (SCL), IC3.17 (SCL), IC4.17 (SCL), IC5.17 (SCL), IC6.17 (SCL), IC7.17 (SCL), IC8.17 (SCL), IC9.17 (SCL), J2.1, J4.1, J6.1, J8.1, J10.1, J12.1, J14.1, J16.1, J18.1
/SDA: IC1.16 (SDA), IC2.16 (SDA), IC3.16 (SDA), IC4.16 (SDA), IC5.16 (SDA), IC6.16 (SDA), IC7.16 (SDA), IC8.16 (SDA), IC9.16 (SDA), J2.2, J4.2, J6.2, J8.2, J10.2, J12.2, J14.2, J16.2, J18.2
GND: IC1.1 (GND_1), IC1.10 (GND_2), IC1.12 (GND_3), IC2.1 (GND_1), IC2.10 (GND_2), IC2.12 (GND_3), IC3.1 (GND_1), IC3.10 (GND_2), IC3.12 (GND_3), IC4.1 (GND_1), IC4.10 (GND_2), IC4.12 (GND_3), IC5.1 (GND_1), IC5.10 (GND_2), IC5.12 (GND_3), IC6.1 (GND_1), IC6.10 (GND_2), IC6.12 (GND_3), IC7.1 (GND_1), IC7.10 (GND_2), IC7.12 (GND_3), IC8.1 (GND_1), IC8.10 (GND_2), IC8.12 (GND_3), IC9.1 (GND_1), IC9.10 (GND_2), IC9.12 (GND_3), J1.5, J3.5, J5.5, J7.5, J9.5, J11.5, J13.5, J15.5, J17.5, U1.1 (minus), U2.1 (minus), U3.1 (minus), U4.1 (minus), U5.1 (minus), U6.1 (minus), U7.1 (minus), U8.1 (minus), U9.1 (minus)
unnamed: ANT1.1, ANT2.1, ANT3.1, ANT4.1, ANT5.1, ANT6.1, ANT7.1, ANT8.1, ANT9.1, IC1.11 (RF_IN), IC2.11 (RF_IN), IC3.11 (RF_IN), IC4.11 (RF_IN), IC5.11 (RF_IN), IC6.11 (RF_IN), IC7.11 (RF_IN), IC8.11 (RF_IN), IC9.11 (RF_IN)
